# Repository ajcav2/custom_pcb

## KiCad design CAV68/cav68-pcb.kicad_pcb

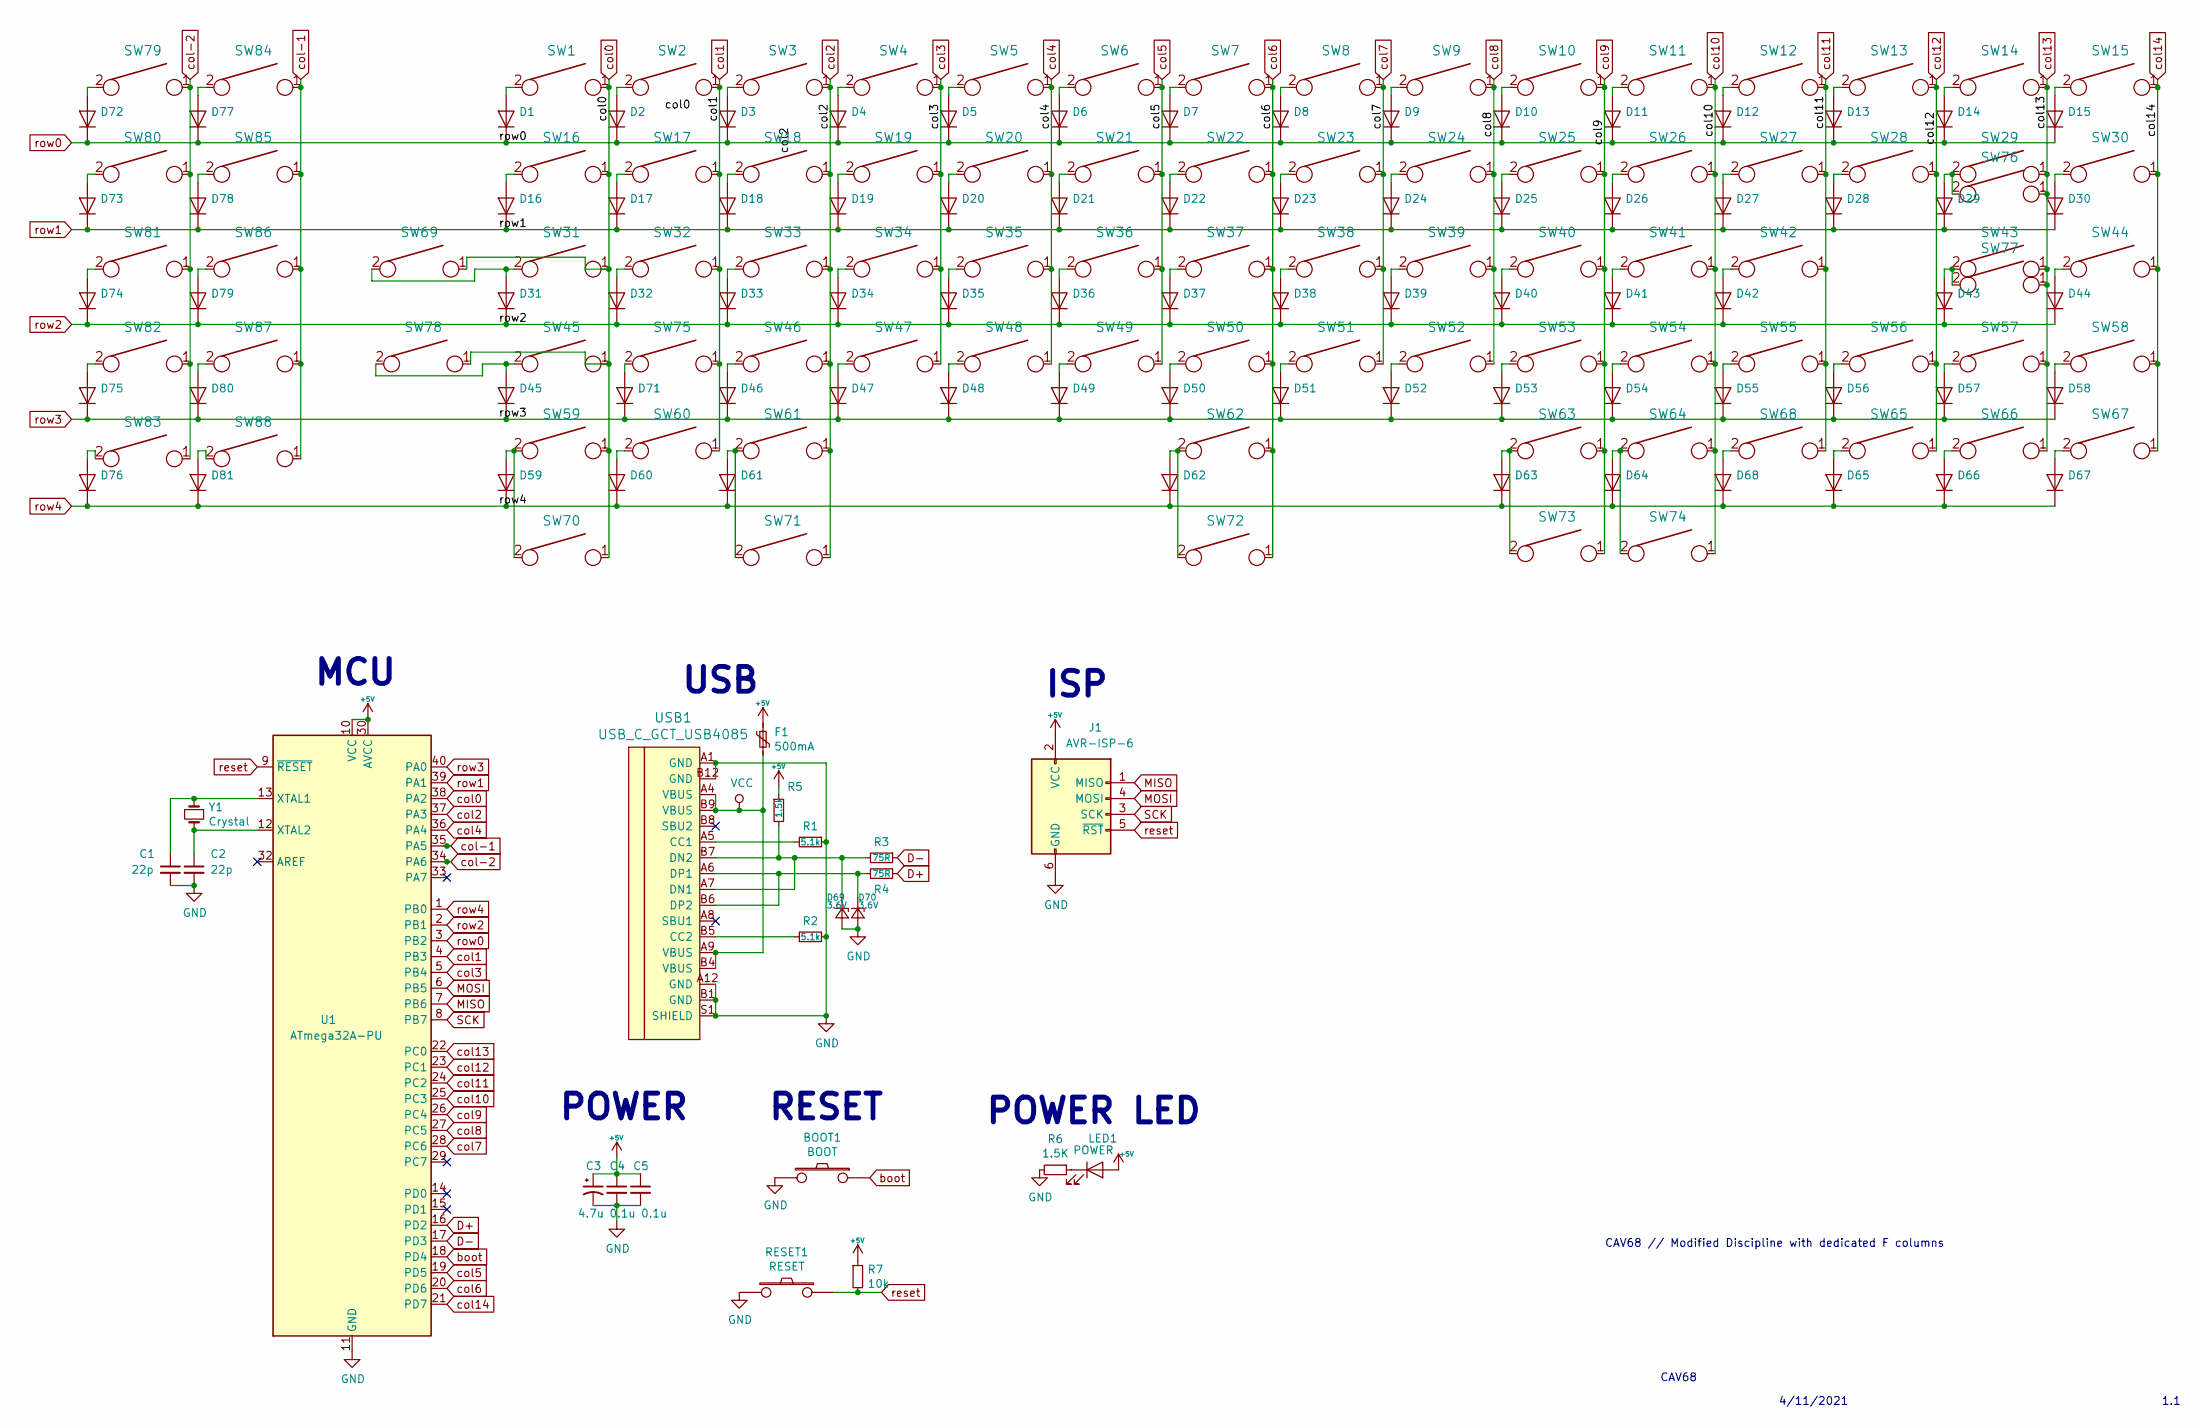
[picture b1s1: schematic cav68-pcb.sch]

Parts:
BOOT1: BOOT; SW_PUSH_6mm
C1, C2: 22p; C_Disc_D3.0mm_W1.6mm_P2.50mm
C3: 4.7u; CP_Radial_D4.0mm_P1.50mm
C4, C5: 0.1u; C_Disc_D4.3mm_W1.9mm_P5.00mm
D1, D2, D3, D4, D5, D6, D7, D8, D9, D10, D11, D12, D13, D14, D15, D16, D17, D18, D19, D20, D21, D22, D23, D24, D25, D26, D27, D28, D29, D30, D31, D32, D33, D34, D35, D36, D37, D38, D39, D40, D41, D42, D43, D44, D45, D46, D47, D48, D49, D50, D51, D52, D53, D54, D55, D56, D57, D58, D59, D60, D61, D62, D63, D64, D65, D66, D67, D68, D71, D72, D73, D74, D75, D76, D77, D78, D79, D80, D81: D_DO-35_SOD27_P5.08mm_Horizontal
D69, D70: 3.6V; D_DO-35_SOD27_P5.08mm_Horizontal
F1: 500mA; polyfuse_5.1mm
J1: AVR-ISP-6; AVR_ICSP_3x2
LED1: POWER; LED_D3.0mm
R1, R2: 5.1k; R_Axial_DIN0204_L3.6mm_D1.6mm_P5.08mm_Horizontal
R3, R4: 75R; R_Axial_DIN0204_L3.6mm_D1.6mm_P5.08mm_Horizontal
R5: 1.5k; R_Axial_DIN0204_L3.6mm_D1.6mm_P5.08mm_Horizontal
R6: 1.5K; R_Axial_DIN0204_L3.6mm_D1.6mm_P5.08mm_Horizontal
R7: 10k; R_Axial_DIN0204_L3.6mm_D1.6mm_P5.08mm_Horizontal
RESET1: RESET; SW_PUSH_6mm
SW1, SW2, SW3, SW4, SW5, SW6, SW7, SW8, SW9, SW10, SW11, SW12, SW13, SW15, SW17, SW18, SW19, SW20, SW21, SW22, SW23, SW24, SW25, SW26, SW27, SW28, SW30, SW32, SW33, SW34, SW35, SW36, SW37, SW38, SW39, SW40, SW41, SW42, SW44, SW46, SW47, SW48, SW49, SW50, SW51, SW52, SW53, SW54, SW55, SW57, SW58, SW62, SW65, SW66, SW67, SW68, SW72, SW75, SW77, SW79, SW80, SW81, SW82, SW83, SW84, SW85, SW86, SW87, SW88: KEYSW; SW_Cherry_MX1A_1.00u_PCB-NOSCREEN
SW14: KEYSW; SW_Cherry_MX1A_2.00u_PCBNOSCREEN
SW16, SW29, SW70, SW71, SW73, SW74: KEYSW; SW_Cherry_MX1A_1.50u_PCBNOSCREEN
SW31, SW56: KEYSW; SW_Cherry_MX1A_1.75u_PCBNOSCREEN
SW43, SW45: KEYSW; SW_Cherry_MX1A_2.25u_PCBNOSCREEN
SW59, SW60, SW61, SW63, SW64, SW69, SW78: KEYSW; SW_Cherry_MX1A_1.25u_PCBNOSCREEN
SW76: KEYSW; SW_Cherry_MX1A_ISOEnter_PCB_ReversedStabilizer
U1: ATmega32A-PU; DIP-40_W15.24mm
USB1: USB_C_GCT_USB4085
Y1: Crystal; Crystal_HC49-4H_Vertical

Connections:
+5V: C3.1, C4.1, C5.1, F1.1, J1.2 (VCC), LED1.2 (A), R5.1, R7.1, U1.10 (VCC), U1.30 (AVCC)
D+: R4.1, U1.16 (PD2)
D-: R3.1, U1.17 (PD3)
GND: BOOT1.1, C1.2, C2.2, C3.2, C4.2, C5.2, D69.2 (A), D70.2 (A), J1.6 (GND), R1.1, R2.2, R6.2, RESET1.1, U1.11 (GND), U1.31 (GND), USB1.A1 (GND), USB1.A12 (GND), USB1.B1 (GND), USB1.B12 (GND), USB1.S1 (SHIELD)
MISO: J1.1 (MISO), U1.7 (PB6)
MOSI: J1.4 (MOSI), U1.6 (PB5)
unnamed: C1.1, U1.13 (XTAL1), Y1.1
unnamed: C2.1, U1.12 (XTAL2), Y1.2
unnamed: D1.2 (A), SW1.2
unnamed: D2.2 (A), SW2.2
unnamed: D3.2 (A), SW3.2
unnamed: D4.2 (A), SW4.2
unnamed: D5.2 (A), SW5.2
unnamed: D6.2 (A), SW6.2
unnamed: D7.2 (A), SW7.2
unnamed: D8.2 (A), SW8.2
unnamed: D9.2 (A), SW9.2
unnamed: D10.2 (A), SW10.2
unnamed: D11.2 (A), SW11.2
unnamed: D12.2 (A), SW12.2
unnamed: D13.2 (A), SW13.2
unnamed: D14.2 (A), SW14.2
unnamed: D15.2 (A), SW15.2
unnamed: D16.2 (A), SW16.2
unnamed: D17.2 (A), SW17.2
unnamed: D18.2 (A), SW18.2
unnamed: D19.2 (A), SW19.2
unnamed: D20.2 (A), SW20.2
unnamed: D21.2 (A), SW21.2
unnamed: D22.2 (A), SW22.2
unnamed: D23.2 (A), SW23.2
unnamed: D24.2 (A), SW24.2
unnamed: D25.2 (A), SW25.2
unnamed: D26.2 (A), SW26.2
unnamed: D27.2 (A), SW27.2
unnamed: D28.2 (A), SW28.2
unnamed: D29.2 (A), SW29.2, SW76.2
unnamed: D30.2 (A), SW30.2
unnamed: D31.2 (A), SW31.2, SW69.2
unnamed: D32.2 (A), SW32.2
unnamed: D33.2 (A), SW33.2
unnamed: D34.2 (A), SW34.2
unnamed: D35.2 (A), SW35.2
unnamed: D36.2 (A), SW36.2
unnamed: D37.2 (A), SW37.2
unnamed: D38.2 (A), SW38.2
unnamed: D39.2 (A), SW39.2
unnamed: D40.2 (A), SW40.2
unnamed: D41.2 (A), SW41.2
unnamed: D42.2 (A), SW42.2
unnamed: D43.2 (A), SW43.2, SW77.2
unnamed: D44.2 (A), SW44.2
unnamed: D45.2 (A), SW45.2, SW78.2
unnamed: D46.2 (A), SW46.2
unnamed: D47.2 (A), SW47.2
unnamed: D48.2 (A), SW48.2
unnamed: D49.2 (A), SW49.2
unnamed: D50.2 (A), SW50.2
unnamed: D51.2 (A), SW51.2
unnamed: D52.2 (A), SW52.2
unnamed: D53.2 (A), SW53.2
unnamed: D54.2 (A), SW54.2
unnamed: D55.2 (A), SW55.2
unnamed: D56.2 (A), SW56.2
unnamed: D57.2 (A), SW57.2
unnamed: D58.2 (A), SW58.2
unnamed: D59.2 (A), SW59.2, SW70.2
unnamed: D60.2 (A), SW60.2
unnamed: D61.2 (A), SW61.2, SW71.2
unnamed: D62.2 (A), SW62.2, SW72.2
unnamed: D63.2 (A), SW63.2, SW73.2
unnamed: D64.2 (A), SW64.2, SW74.2
unnamed: D65.2 (A), SW65.2
unnamed: D66.2 (A), SW66.2
unnamed: D67.2 (A), SW67.2
unnamed: D68.2 (A), SW68.2
unnamed: D69.1 (K), R3.2, R5.2, USB1.A7 (DN1), USB1.B7 (DN2)
unnamed: D70.1 (K), R4.2, USB1.A6 (DP1), USB1.B6 (DP2)
unnamed: D71.2 (A), SW75.2
unnamed: D72.2 (A), SW79.2
unnamed: D73.2 (A), SW80.2
unnamed: D74.2 (A), SW81.2
unnamed: D75.2 (A), SW82.2
unnamed: D76.2 (A), SW83.2
unnamed: D77.2 (A), SW84.2
unnamed: D78.2 (A), SW85.2
unnamed: D79.2 (A), SW86.2
unnamed: D80.2 (A), SW87.2
unnamed: D81.2 (A), SW88.2
unnamed: LED1.1 (K), R6.1
unnamed: R1.2, USB1.A5 (CC1)
unnamed: R2.1, USB1.B5 (CC2)
SCK: J1.3 (SCK), U1.8 (PB7)
VCC: F1.2, USB1.A4 (VBUS), USB1.A9 (VBUS), USB1.B4 (VBUS), USB1.B9 (VBUS)
boot: BOOT1.2, U1.18 (PD4)
col0: SW1.1, SW16.1, SW31.1, SW45.1, SW59.1, SW69.1, SW70.1, SW78.1, U1.38 (PA2)
col1: SW2.1, SW17.1, SW32.1, SW60.1, SW75.1, U1.4 (PB3)
col2: SW3.1, SW18.1, SW33.1, SW46.1, SW61.1, SW71.1, U1.37 (PA3)
col3: SW4.1, SW19.1, SW34.1, SW47.1, U1.5 (PB4)
col4: SW5.1, SW20.1, SW35.1, SW48.1, U1.36 (PA4)
col5: SW6.1, SW21.1, SW36.1, SW49.1, U1.19 (PD5)
col6: SW7.1, SW22.1, SW37.1, SW50.1, SW62.1, SW72.1, U1.20 (PD6)
col7: SW8.1, SW23.1, SW38.1, SW51.1, U1.28 (PC6)
col8: SW9.1, SW24.1, SW39.1, SW52.1, U1.27 (PC5)
col9: SW10.1, SW25.1, SW40.1, SW53.1, SW63.1, SW73.1, U1.26 (PC4)
col10: SW11.1, SW26.1, SW41.1, SW54.1, SW64.1, SW74.1, U1.25 (PC3)
col11: SW12.1, SW27.1, SW42.1, SW55.1, SW68.1, U1.24 (PC2)
col12: SW13.1, SW28.1, SW56.1, SW65.1, U1.23 (PC1)
col13: SW14.1, SW29.1, SW43.1, SW57.1, SW66.1, SW76.1, SW77.1, U1.22 (PC0)
col14: SW15.1, SW30.1, SW44.1, SW58.1, SW67.1, U1.21 (PD7)
col-1: SW84.1, SW85.1, SW86.1, SW87.1, SW88.1, U1.35 (PA5)
col-2: SW79.1, SW80.1, SW81.1, SW82.1, SW83.1, U1.34 (PA6)
reset: J1.5 (~RST), R7.2, RESET1.2, U1.9 (~RESET)
row0: D1.1 (K), D2.1 (K), D3.1 (K), D4.1 (K), D5.1 (K), D6.1 (K), D7.1 (K), D8.1 (K), D9.1 (K), D10.1 (K), D11.1 (K), D12.1 (K), D13.1 (K), D14.1 (K), D15.1 (K), D72.1 (K), D77.1 (K), U1.3 (PB2)
row1: D16.1 (K), D17.1 (K), D18.1 (K), D19.1 (K), D20.1 (K), D21.1 (K), D22.1 (K), D23.1 (K), D24.1 (K), D25.1 (K), D26.1 (K), D27.1 (K), D28.1 (K), D29.1 (K), D30.1 (K), D73.1 (K), D78.1 (K), U1.39 (PA1)
row2: D31.1 (K), D32.1 (K), D33.1 (K), D34.1 (K), D35.1 (K), D36.1 (K), D37.1 (K), D38.1 (K), D39.1 (K), D40.1 (K), D41.1 (K), D42.1 (K), D43.1 (K), D44.1 (K), D74.1 (K), D79.1 (K), U1.2 (PB1)
row3: D45.1 (K), D46.1 (K), D47.1 (K), D48.1 (K), D49.1 (K), D50.1 (K), D51.1 (K), D52.1 (K), D53.1 (K), D54.1 (K), D55.1 (K), D56.1 (K), D57.1 (K), D58.1 (K), D71.1 (K), D75.1 (K), D80.1 (K), U1.40 (PA0)
row4: D59.1 (K), D60.1 (K), D61.1 (K), D62.1 (K), D63.1 (K), D64.1 (K), D65.1 (K), D66.1 (K), D67.1 (K), D68.1 (K), D76.1 (K), D81.1 (K), U1.1 (PB0)

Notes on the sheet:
4/11/2021
CAV68
1.1
MCU
USB
ISP
POWER
RESET
POWER LED
CAV68 // Modified Discipline with dedicated F columns

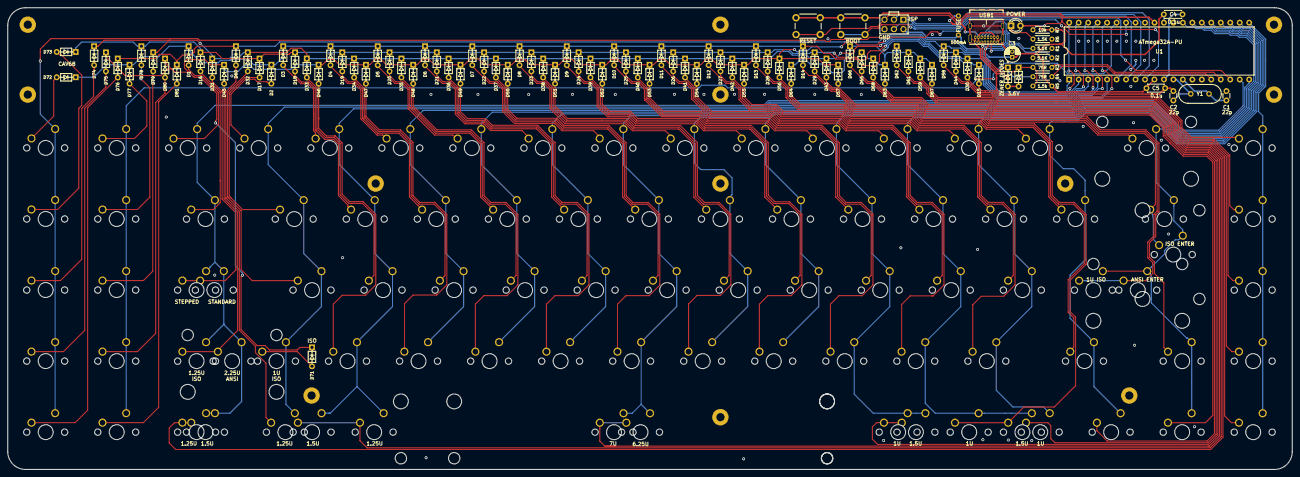
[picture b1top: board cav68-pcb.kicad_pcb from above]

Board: 2 copper layers, 344.5 x 123.8 mm, 190 parts (0 on the bottom side), 118 nets.

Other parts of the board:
ST72: 7U; MX-7U-Stabilizer

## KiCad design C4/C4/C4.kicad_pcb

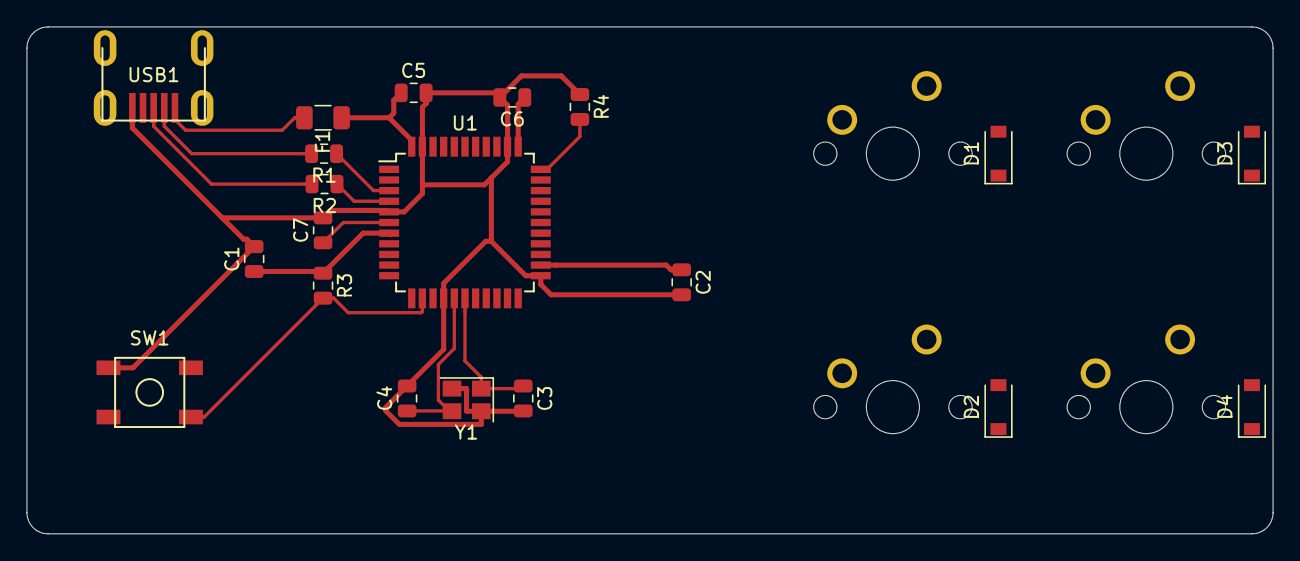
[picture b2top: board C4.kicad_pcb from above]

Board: 2 copper layers, 93.7 x 38.1 mm, 24 parts (0 on the bottom side), 20 nets.

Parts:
C1, C2, C5: 0.1uF; C_0805_2012Metric
C3, C4: 22pF; C_0805_2012Metric
C6: 10uF; C_0805_2012Metric
C7: 1uF; C_0805_2012Metric
D1, D2, D3, D4: SOD_123; D_SOD-123
F1: 500mA; Fuse_1206_3216Metric
MX1, MX2, MX3, MX4: MX-NoLED; MXOnly-1U-NoLED
R1, R2: 22; R_0805_2012Metric
R3, R4: 10k; R_0805_2012Metric
SW1: SW_Push; SKQG-1155865
U1: ATmega32U4-AU; TQFP-44_10x10mm_P0.8mm
USB1: Molex-0548190589
Y1: 16MHz; Crystal_SMD_3225-4Pin_3.2x2.5mm

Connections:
+5V: C1.1, C2.1, C5.1, C6.1, F1.1, R3.1, U1.2, U1.7, U1.14, U1.24, U1.34, U1.44
COL1: MX3.1, MX4.1
D+: R2.2, USB1.3
D-: R1.2, USB1.4
GND: C1.2, C2.2, C3.2, C4.2, C5.2, C6.2, C7.2, R4.1, SW1.1, U1.5, U1.15, U1.23, U1.35, U1.43, USB1.1, Y1.2, Y1.4
unnamed: C3.1, U1.17, Y1.1
unnamed: C4.1, U1.16, Y1.3
unnamed: C7.1, U1.6
unnamed: D1.2, MX1.2
unnamed: D2.2, MX2.2
unnamed: D3.2, MX3.2
unnamed: D4.2, MX4.2
unnamed: MX1.1, MX2.1
unnamed: R1.1, U1.3
unnamed: R2.1, U1.4
unnamed: R3.2, SW1.2, U1.13
unnamed: R4.2, U1.33
ROW0: D1.1, D3.1
ROW1: D2.1, D4.1
VCC: F1.2, USB1.5

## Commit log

2021-04-10 init
2021-04-10 Add submodules
2021-04-10 moving modules
2021-04-11 Adding CAV68
2021-04-11 Moving diode lables to top silkscreen
